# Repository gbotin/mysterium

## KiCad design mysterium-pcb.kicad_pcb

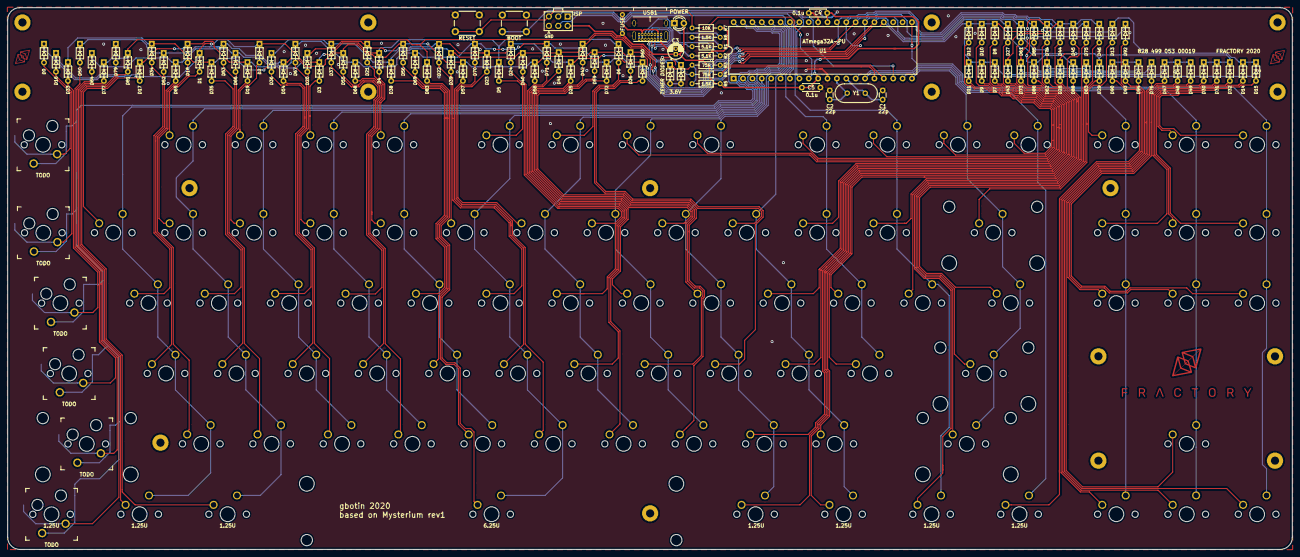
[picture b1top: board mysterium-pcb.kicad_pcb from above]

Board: 2 copper layers, 347.7 x 146.6 mm, 197 parts (0 on the bottom side), 128 nets.

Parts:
BOOT1: BOOT; SW_PUSH_6mm
C1, C2: 22p; C_Disc_D3.0mm_W1.6mm_P2.50mm
C3: 4.7u; CP_Radial_D4.0mm_P1.50mm
C4, C5: 0.1u; C_Disc_D4.3mm_W1.9mm_P5.00mm
D0, D1, D2, D3, D4, D5, D6, D7, D8, D9, D10, D11, D12, D13, D14, D15, D16, D17, D18, D19, D20, D21, D22, D23, D24, D25, D26, D27, D28, D29, D30, D31, D32, D33, D34, D35, D36, D37, D38, D39, D40, D41, D42, D43, D44, D45, D46, D47, D48, D49, D50, D52, D53, D54, D55, D56, D57, D58, D59, D60, D61, D62, D63, D64, D65, D66, D67, D68, D69, D70, D71, D72, D73, D74, D75, D76, D77, D79, D81, D83, D85, D86, D88, D90, D92, D93, D94: D_Small; D_DO-35_SOD27_P5.08mm_Horizontal
D95, D96: 3.6V; D_DO-35_SOD27_P5.08mm_Horizontal
F1: 500mA; polyfuse_5.1mm
J1: AVR-ISP-6; AVR_ICSP_3x2
LED1: POWER; LED_D3.0mm
R1, R2: 5.1K; R_Axial_DIN0204_L3.6mm_D1.6mm_P7.62mm_Horizontal
R3, R4: 75R; R_Axial_DIN0204_L3.6mm_D1.6mm_P7.62mm_Horizontal
R5, R6: 1.5K; R_Axial_DIN0204_L3.6mm_D1.6mm_P7.62mm_Horizontal
R7: 10K; R_Axial_DIN0204_L3.6mm_D1.6mm_P7.62mm_Horizontal
RESET1: RESET; SW_PUSH_6mm
ST83: 6.25U; MX-6.25U-Stabilizer
SW1, SW2, SW3, SW4, SW5, SW6, SW7, SW8, SW9, SW10, SW11, SW12, SW13, SW14, SW15, SW17, SW18, SW19, SW20, SW21, SW22, SW23, SW24, SW25, SW26, SW27, SW28, SW30, SW31, SW32, SW34, SW35, SW36, SW37, SW38, SW39, SW40, SW41, SW42, SW43, SW44, SW45, SW47, SW48, SW49, SW52, SW53, SW54, SW55, SW56, SW57, SW58, SW59, SW60, SW61, SW62, SW65, SW66, SW67, SW68, SW69, SW70, SW71, SW72, SW73, SW74, SW76, SW83, SW92, SW93, SW94: KEYSW; SW_Cherry_MX1A_1.00u_PCB-NOSCREEN
SW29: KEYSW; SW_Cherry_MX1A_2.00u_PCBNOSCREEN
SW46: KEYSW; SW_Cherry_MX1A_1.50u_PCBNOSCREEN
SW63: KEYSW; SW_Cherry_MX1A_2.25u_PCBNOSCREEN
SW75: KEYSW; SW_Cherry_MX1A_2.75u_PCB_NOSCREEN
SW79, SW82, SW85, SW87, SW88, SW91: KEYSW; SW_Cherry_MX1A_1.25u_PCBNOSCREEN
TODO: SW50; Kailh_socket_MX_optional_reversed
TODO#2: SW16; Kailh_socket_MX_optional_reversed
TODO#3: SW0; Kailh_socket_MX_optional_reversed
TODO#4: SW64; Kailh_socket_MX_optional_reversed
TODO#5: SW78; Kailh_socket_MX_optional_reversed
TODO#6: SW33; Kailh_socket_MX_optional_reversed
U1: ATmega32A-PU; DIP-40_W15.24mm
USB1: USB_C_GCT_USB4085
Y1: Crystal; Crystal_HC49-4H_Vertical

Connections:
+5V: C3.1, C4.1, C5.1, F1.1, J1.2, LED1.2, R5.1, R7.1, U1.10, U1.30
D+: R4.1, U1.16
D-: R3.1, U1.17
GND: BOOT1.1, C1.2, C2.2, C3.2, C4.2, C5.2, D95.2, D96.2, J1.6, R1.1, R2.2, R6.2, RESET1.1, U1.11, U1.31, USB1.A1, USB1.A12, USB1.B1, USB1.B12, USB1.S1
MISO: J1.1, U1.7
MOSI: J1.4, U1.6
unnamed: C1.1, U1.13, Y1.1
unnamed: C2.1, U1.12, Y1.2
unnamed: D0.2, TODO#3.2
unnamed: D1.2, SW1.2
unnamed: D2.2, SW2.2
unnamed: D3.2, SW3.2
unnamed: D4.2, SW4.2
unnamed: D5.2, SW5.2
unnamed: D6.2, SW6.2
unnamed: D7.2, SW7.2
unnamed: D8.2, SW8.2
unnamed: D9.2, SW9.2
unnamed: D10.2, SW10.2
unnamed: D11.2, SW11.2
unnamed: D12.2, SW12.2
unnamed: D13.2, SW13.2
unnamed: D14.2, SW14.2
unnamed: D15.2, SW15.2
unnamed: D16.2, TODO#2.2
unnamed: D17.2, SW17.2
unnamed: D18.2, SW18.2
unnamed: D19.2, SW19.2
unnamed: D20.2, SW20.2
unnamed: D21.2, SW21.2
unnamed: D22.2, SW22.2
unnamed: D23.2, SW23.2
unnamed: D24.2, SW24.2
unnamed: D25.2, SW25.2
unnamed: D26.2, SW26.2
unnamed: D27.2, SW27.2
unnamed: D28.2, SW28.2
unnamed: D29.2, SW29.2
unnamed: D30.2, SW30.2
unnamed: D31.2, SW31.2
unnamed: D32.2, SW32.2
unnamed: D33.2, TODO#6.2
unnamed: D34.2, SW34.2
unnamed: D35.2, SW35.2
unnamed: D36.2, SW36.2
unnamed: D37.2, SW37.2
unnamed: D38.2, SW38.2
unnamed: D39.2, SW39.2
unnamed: D40.2, SW40.2
unnamed: D41.2, SW41.2
unnamed: D42.2, SW42.2
unnamed: D43.2, SW43.2
unnamed: D44.2, SW44.2
unnamed: D45.2, SW45.2
unnamed: D46.2, SW46.2
unnamed: D47.2, SW47.2
unnamed: D48.2, SW48.2
unnamed: D49.2, SW49.2
unnamed: D50.2, TODO.2
unnamed: D52.2, SW52.2
unnamed: D53.2, SW53.2
unnamed: D54.2, SW54.2
unnamed: D55.2, SW55.2
unnamed: D56.2, SW56.2
unnamed: D57.2, SW57.2
unnamed: D58.2, SW58.2
unnamed: D59.2, SW59.2
unnamed: D60.2, SW60.2
unnamed: D61.2, SW61.2
unnamed: D62.2, SW62.2
unnamed: D63.2, SW63.2
unnamed: D64.2, TODO#4.2
unnamed: D65.2, SW65.2
unnamed: D66.2, SW66.2
unnamed: D67.2, SW67.2
unnamed: D68.2, SW68.2
unnamed: D69.2, SW69.2
unnamed: D70.2, SW70.2
unnamed: D71.2, SW71.2
unnamed: D72.2, SW72.2
unnamed: D73.2, SW73.2
unnamed: D74.2, SW74.2
unnamed: D75.2, SW75.2
unnamed: D76.2, SW76.2
unnamed: D77.2, TODO#5.2
unnamed: D79.2, SW79.2
unnamed: D81.2, SW82.2
unnamed: D83.2, SW83.2
unnamed: D85.2, SW85.2
unnamed: D86.2, SW87.2
unnamed: D88.2, SW88.2
unnamed: D90.2, SW91.2
unnamed: D92.2, SW92.2
unnamed: D93.2, SW93.2
unnamed: D94.2, SW94.2
unnamed: D95.1, R3.2, R5.2, USB1.A7, USB1.B7
unnamed: D96.1, R4.2, USB1.A6, USB1.B6
unnamed: LED1.1, R6.1
unnamed: R1.2, USB1.A5
unnamed: R2.1, USB1.B5
SCK: J1.3, U1.8
VCC: F1.2, USB1.A4, USB1.A9, USB1.B4, USB1.B9
boot: BOOT1.2, U1.18
col0: TODO.1, TODO#2.1, TODO#3.1, TODO#4.1, TODO#5.1, TODO#6.1, U1.40
col1: SW17.1, SW34.1, SW52.1, SW65.1, SW79.1, U1.1
col2: SW1.1, SW18.1, SW35.1, SW53.1, SW66.1, SW82.1, U1.39
col3: SW2.1, SW19.1, SW36.1, SW54.1, SW67.1, U1.2
col4: SW3.1, SW20.1, SW37.1, SW55.1, SW68.1, U1.38
col5: SW4.1, SW21.1, SW38.1, SW56.1, SW69.1, U1.3
col6: SW5.1, SW22.1, SW39.1, SW57.1, SW70.1, SW83.1, U1.37
col7: SW6.1, SW23.1, SW40.1, SW58.1, SW71.1, U1.4
col8: SW7.1, SW24.1, SW41.1, SW59.1, SW72.1, U1.36
col9: SW8.1, SW25.1, SW42.1, SW60.1, SW73.1, SW85.1, U1.5
col10: SW26.1, SW43.1, SW61.1, SW74.1, SW87.1, U1.35
col11: SW9.1, SW27.1, SW44.1, SW62.1, U1.34
col12: SW10.1, SW28.1, SW45.1, SW88.1, U1.33
col13: SW11.1, SW29.1, SW46.1, SW63.1, SW75.1, U1.20
col14: SW12.1, SW91.1, U1.19
col15: SW13.1, SW30.1, SW47.1, SW92.1, U1.15
col16: SW14.1, SW31.1, SW48.1, SW76.1, SW93.1, U1.14
col17: SW15.1, SW32.1, SW49.1, SW94.1, U1.21
reset: J1.5, R7.2, RESET1.2, U1.9
row0: D0.1, D1.1, D2.1, D3.1, D4.1, D5.1, D6.1, D7.1, D8.1, D9.1, D10.1, D11.1, D12.1, D13.1, D14.1, D15.1, U1.24
row1: D16.1, D17.1, D18.1, D19.1, D20.1, D21.1, D22.1, D23.1, D24.1, D25.1, D26.1, D27.1, D28.1, D29.1, D30.1, D31.1, D32.1, U1.25
row2: D33.1, D34.1, D35.1, D36.1, D37.1, D38.1, D39.1, D40.1, D41.1, D42.1, D43.1, D44.1, D45.1, D46.1, D47.1, D48.1, D49.1, U1.29
row3: D50.1, D52.1, D53.1, D54.1, D55.1, D56.1, D57.1, D58.1, D59.1, D60.1, D61.1, D62.1, D63.1, U1.26
row4: D64.1, D65.1, D66.1, D67.1, D68.1, D69.1, D70.1, D71.1, D72.1, D73.1, D74.1, D75.1, D76.1, U1.28
row5: D77.1, D79.1, D81.1, D83.1, D85.1, D86.1, D88.1, D90.1, D92.1, D93.1, D94.1, U1.27

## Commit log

2020-05-03 Add Fractory footprints
2020-05-03 Update decorations / Add new switches lib
2020-05-03 Remove Stepped Caps lock footprint
2020-05-03 Remove 1.5u ctrl footprint
2020-05-03 Remove 1u win footprint
2020-05-03 Remove 1.5u alt footprint
2020-05-03 Remove 1.5u right ctrl footprint
2020-05-03 Keep 1.25u meta footprint
2020-05-03 Remove 1.5u right win footprint
2020-05-03 Remove 7u spacebar footprint
2020-05-03 Fix left ctrl connection
2020-05-03 Update Kailh socket MX footprint to match mysterium switch actual center
2020-05-03 Add reversed Kailh socket MM optionnal
2020-05-03 Update SW0
2020-05-03 Finish updating Col0 with Kailh sockets
2020-05-10 Update Switch Sockets with 3 shapes / Update Col0 wiring
